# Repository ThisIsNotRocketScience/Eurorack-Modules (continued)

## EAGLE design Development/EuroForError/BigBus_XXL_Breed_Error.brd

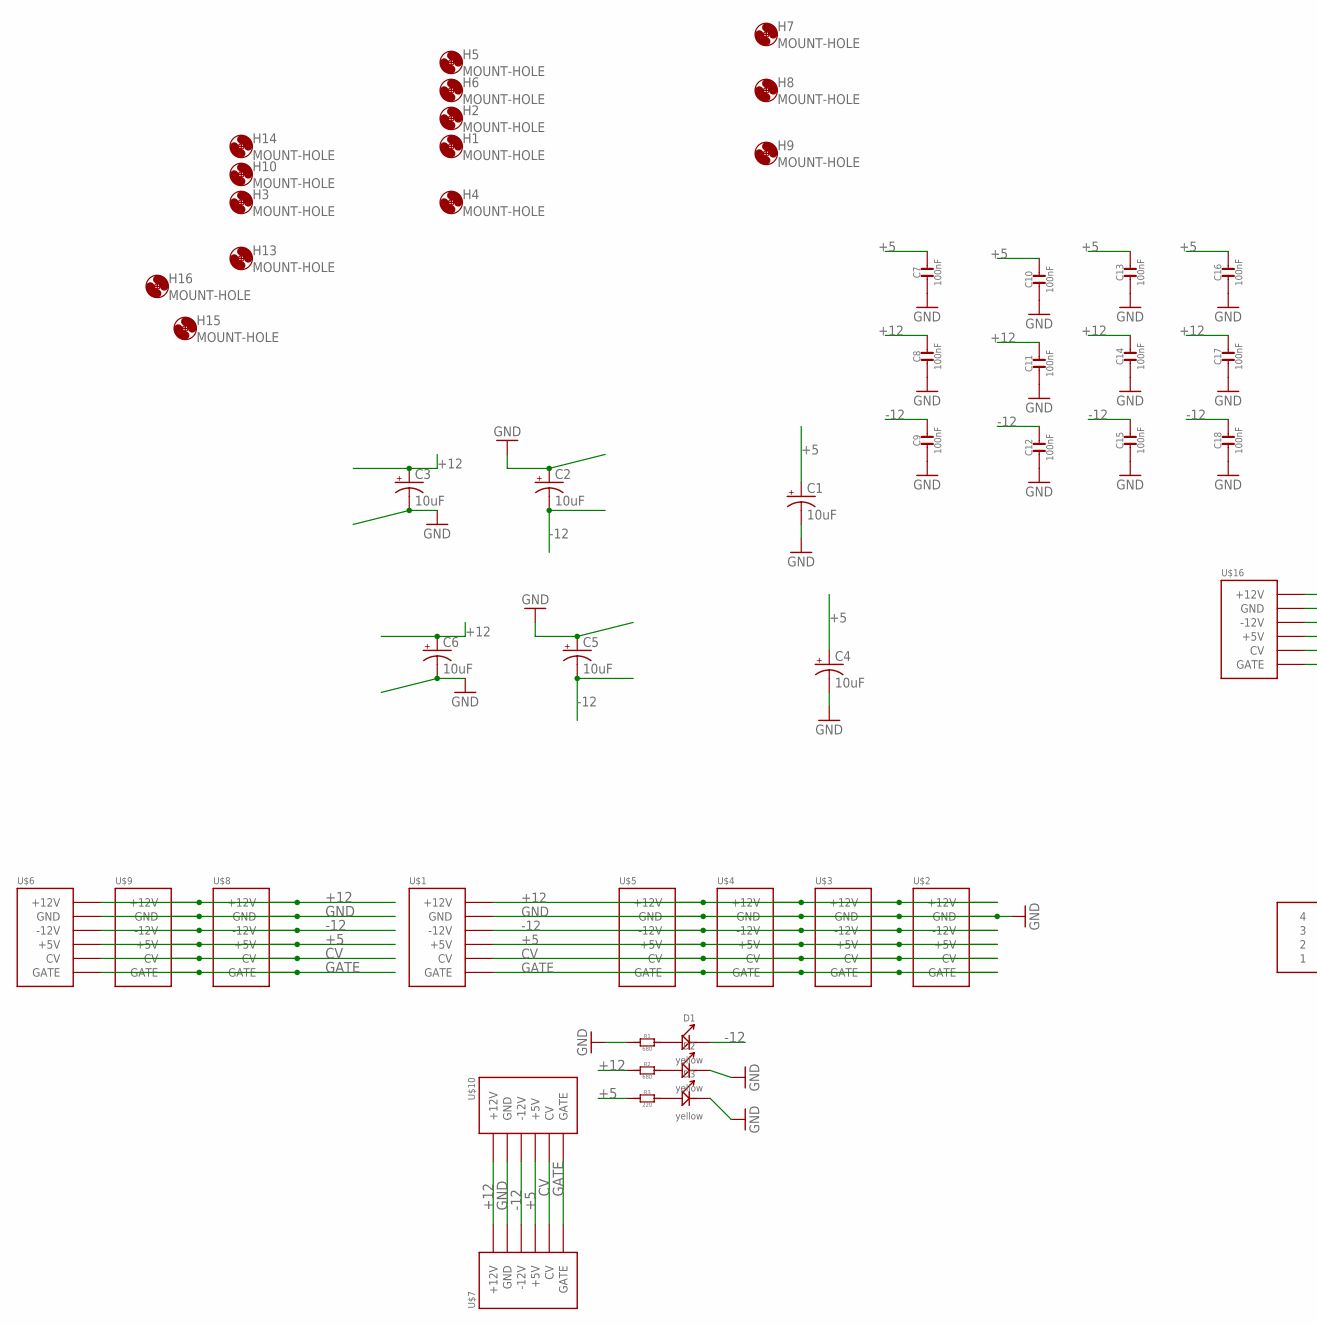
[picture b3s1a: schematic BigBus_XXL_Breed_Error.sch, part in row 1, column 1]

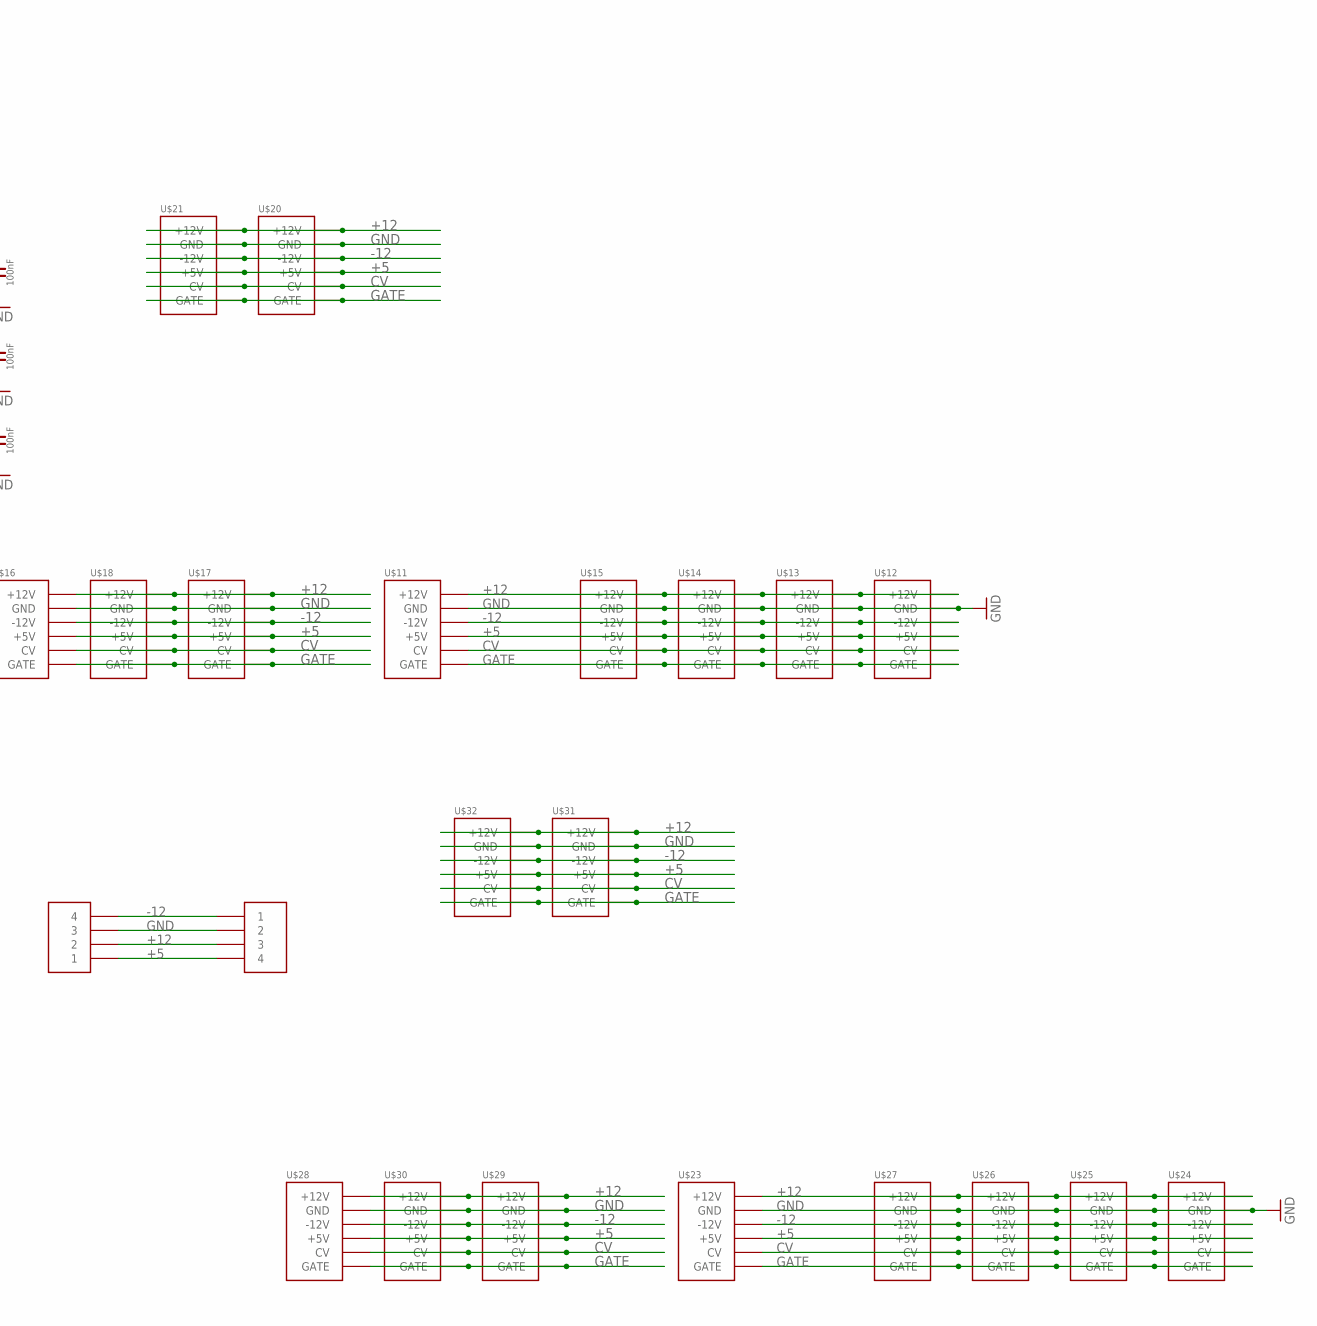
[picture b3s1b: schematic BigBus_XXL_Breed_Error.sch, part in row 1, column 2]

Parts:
C1, C2, C3, C4, C5, C6: 10uF; PANASONIC_D
C7, C8, C9, C10, C11, C12, C13, C14, C15, C16, C17, C18: 100nF; C0603
D1, D2, D3: yellow; LED0603
H1, H2, H3, H4, H5, H6, H7, H8, H9, H10, H13, H14, H15, H16: MOUNT-HOLE; 3.2-NOMARKINGS-SMALLSAFEZONE
R1, R2: 680; R0603
R3: 220; R0603
U$1, U$2, U$3, U$4, U$5, U$6, U$7, U$8, U$9, U$10, U$11, U$12, U$13, U$14, U$15, U$16, U$17, U$18, U$20, U$21, U$23, U$24, U$25, U$26, U$27, U$28, U$29, U$30, U$31, U$32: POWER_SHROUDED_NOTEXT; POWER_16_SHROUDED_NOTEXT
U$19, U$22: 4PIN5MM

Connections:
+5: C1.+, C4.+, C7.2, C10.2, C13.2, C16.2, R3.1, U$1.11 (+5V), U$1.12 (+5V), U$2.11 (+5V), U$2.12 (+5V), U$3.11 (+5V), U$3.12 (+5V), U$4.11 (+5V), U$4.12 (+5V), U$5.11 (+5V), U$5.12 (+5V), U$6.11 (+5V), U$6.12 (+5V), U$7.11 (+5V), U$7.12 (+5V), U$8.11 (+5V), U$8.12 (+5V), U$9.11 (+5V), U$9.12 (+5V), U$10.11 (+5V), U$10.12 (+5V), U$11.11 (+5V), U$11.12 (+5V), U$12.11 (+5V), U$12.12 (+5V), U$13.11 (+5V), U$13.12 (+5V), U$14.11 (+5V), U$14.12 (+5V), U$15.11 (+5V), U$15.12 (+5V), U$16.11 (+5V), U$16.12 (+5V), U$17.11 (+5V), U$17.12 (+5V), U$18.11 (+5V), U$18.12 (+5V), U$19.4, U$20.11 (+5V), U$20.12 (+5V), U$21.11 (+5V), U$21.12 (+5V), U$22.1, U$23.11 (+5V), U$23.12 (+5V), U$24.11 (+5V), U$24.12 (+5V), U$25.11 (+5V), U$25.12 (+5V), U$26.11 (+5V), U$26.12 (+5V), U$27.11 (+5V), U$27.12 (+5V), U$28.11 (+5V), U$28.12 (+5V), U$29.11 (+5V), U$29.12 (+5V), U$30.11 (+5V), U$30.12 (+5V), U$31.11 (+5V), U$31.12 (+5V), U$32.11 (+5V), U$32.12 (+5V)
+12: C3.+, C6.+, C8.2, C11.2, C14.2, C17.2, R2.1, U$1.9 (+12V), U$1.10 (+12V), U$2.9 (+12V), U$2.10 (+12V), U$3.9 (+12V), U$3.10 (+12V), U$4.9 (+12V), U$4.10 (+12V), U$5.9 (+12V), U$5.10 (+12V), U$6.9 (+12V), U$6.10 (+12V), U$7.9 (+12V), U$7.10 (+12V), U$8.9 (+12V), U$8.10 (+12V), U$9.9 (+12V), U$9.10 (+12V), U$10.9 (+12V), U$10.10 (+12V), U$11.9 (+12V), U$11.10 (+12V), U$12.9 (+12V), U$12.10 (+12V), U$13.9 (+12V), U$13.10 (+12V), U$14.9 (+12V), U$14.10 (+12V), U$15.9 (+12V), U$15.10 (+12V), U$16.9 (+12V), U$16.10 (+12V), U$17.9 (+12V), U$17.10 (+12V), U$18.9 (+12V), U$18.10 (+12V), U$19.3, U$20.9 (+12V), U$20.10 (+12V), U$21.9 (+12V), U$21.10 (+12V), U$22.2, U$23.9 (+12V), U$23.10 (+12V), U$24.9 (+12V), U$24.10 (+12V), U$25.9 (+12V), U$25.10 (+12V), U$26.9 (+12V), U$26.10 (+12V), U$27.9 (+12V), U$27.10 (+12V), U$28.9 (+12V), U$28.10 (+12V), U$29.9 (+12V), U$29.10 (+12V), U$30.9 (+12V), U$30.10 (+12V), U$31.9 (+12V), U$31.10 (+12V), U$32.9 (+12V), U$32.10 (+12V)
-12: C2.-, C5.-, C9.2, C12.2, C15.2, C18.2, D1.-, U$1.1 (-12V), U$1.2 (-12V), U$2.1 (-12V), U$2.2 (-12V), U$3.1 (-12V), U$3.2 (-12V), U$4.1 (-12V), U$4.2 (-12V), U$5.1 (-12V), U$5.2 (-12V), U$6.1 (-12V), U$6.2 (-12V), U$7.1 (-12V), U$7.2 (-12V), U$8.1 (-12V), U$8.2 (-12V), U$9.1 (-12V), U$9.2 (-12V), U$10.1 (-12V), U$10.2 (-12V), U$11.1 (-12V), U$11.2 (-12V), U$12.1 (-12V), U$12.2 (-12V), U$13.1 (-12V), U$13.2 (-12V), U$14.1 (-12V), U$14.2 (-12V), U$15.1 (-12V), U$15.2 (-12V), U$16.1 (-12V), U$16.2 (-12V), U$17.1 (-12V), U$17.2 (-12V), U$18.1 (-12V), U$18.2 (-12V), U$19.1, U$20.1 (-12V), U$20.2 (-12V), U$21.1 (-12V), U$21.2 (-12V), U$22.4, U$23.1 (-12V), U$23.2 (-12V), U$24.1 (-12V), U$24.2 (-12V), U$25.1 (-12V), U$25.2 (-12V), U$26.1 (-12V), U$26.2 (-12V), U$27.1 (-12V), U$27.2 (-12V), U$28.1 (-12V), U$28.2 (-12V), U$29.1 (-12V), U$29.2 (-12V), U$30.1 (-12V), U$30.2 (-12V), U$31.1 (-12V), U$31.2 (-12V), U$32.1 (-12V), U$32.2 (-12V)
CV: U$1.13 (CV), U$1.14 (CV), U$2.13 (CV), U$2.14 (CV), U$3.13 (CV), U$3.14 (CV), U$4.13 (CV), U$4.14 (CV), U$5.13 (CV), U$5.14 (CV), U$6.13 (CV), U$6.14 (CV), U$7.13 (CV), U$7.14 (CV), U$8.13 (CV), U$8.14 (CV), U$9.13 (CV), U$9.14 (CV), U$10.13 (CV), U$10.14 (CV), U$11.13 (CV), U$11.14 (CV), U$12.13 (CV), U$12.14 (CV), U$13.13 (CV), U$13.14 (CV), U$14.13 (CV), U$14.14 (CV), U$15.13 (CV), U$15.14 (CV), U$16.13 (CV), U$16.14 (CV), U$17.13 (CV), U$17.14 (CV), U$18.13 (CV), U$18.14 (CV), U$20.13 (CV), U$20.14 (CV), U$21.13 (CV), U$21.14 (CV), U$23.13 (CV), U$23.14 (CV), U$24.13 (CV), U$24.14 (CV), U$25.13 (CV), U$25.14 (CV), U$26.13 (CV), U$26.14 (CV), U$27.13 (CV), U$27.14 (CV), U$28.13 (CV), U$28.14 (CV), U$29.13 (CV), U$29.14 (CV), U$30.13 (CV), U$30.14 (CV), U$31.13 (CV), U$31.14 (CV), U$32.13 (CV), U$32.14 (CV)
GATE: U$1.15 (GATE), U$1.16 (GATE), U$2.15 (GATE), U$2.16 (GATE), U$3.15 (GATE), U$3.16 (GATE), U$4.15 (GATE), U$4.16 (GATE), U$5.15 (GATE), U$5.16 (GATE), U$6.15 (GATE), U$6.16 (GATE), U$7.15 (GATE), U$7.16 (GATE), U$8.15 (GATE), U$8.16 (GATE), U$9.15 (GATE), U$9.16 (GATE), U$10.15 (GATE), U$10.16 (GATE), U$11.15 (GATE), U$11.16 (GATE), U$12.15 (GATE), U$12.16 (GATE), U$13.15 (GATE), U$13.16 (GATE), U$14.15 (GATE), U$14.16 (GATE), U$15.15 (GATE), U$15.16 (GATE), U$16.15 (GATE), U$16.16 (GATE), U$17.15 (GATE), U$17.16 (GATE), U$18.15 (GATE), U$18.16 (GATE), U$20.15 (GATE), U$20.16 (GATE), U$21.15 (GATE), U$21.16 (GATE), U$23.15 (GATE), U$23.16 (GATE), U$24.15 (GATE), U$24.16 (GATE), U$25.15 (GATE), U$25.16 (GATE), U$26.15 (GATE), U$26.16 (GATE), U$27.15 (GATE), U$27.16 (GATE), U$28.15 (GATE), U$28.16 (GATE), U$29.15 (GATE), U$29.16 (GATE), U$30.15 (GATE), U$30.16 (GATE), U$31.15 (GATE), U$31.16 (GATE), U$32.15 (GATE), U$32.16 (GATE)
GND: C1.-, C2.+, C3.-, C4.-, C5.+, C6.-, C7.1, C8.1, C9.1, C10.1, C11.1, C12.1, C13.1, C14.1, C15.1, C16.1, C17.1, C18.1, D2.-, D3.-, R1.1, U$1.3 (GND), U$1.4 (GND), U$1.5 (GND), U$1.6 (GND), U$1.7 (GND), U$1.8 (GND), U$2.3 (GND), U$2.4 (GND), U$2.5 (GND), U$2.6 (GND), U$2.7 (GND), U$2.8 (GND), U$3.3 (GND), U$3.4 (GND), U$3.5 (GND), U$3.6 (GND), U$3.7 (GND), U$3.8 (GND), U$4.3 (GND), U$4.4 (GND), U$4.5 (GND), U$4.6 (GND), U$4.7 (GND), U$4.8 (GND), U$5.3 (GND), U$5.4 (GND), U$5.5 (GND), U$5.6 (GND), U$5.7 (GND), U$5.8 (GND), U$6.3 (GND), U$6.4 (GND), U$6.5 (GND), U$6.6 (GND), U$6.7 (GND), U$6.8 (GND), U$7.3 (GND), U$7.4 (GND), U$7.5 (GND), U$7.6 (GND), U$7.7 (GND), U$7.8 (GND), U$8.3 (GND), U$8.4 (GND), U$8.5 (GND), U$8.6 (GND), U$8.7 (GND), U$8.8 (GND), U$9.3 (GND), U$9.4 (GND), U$9.5 (GND), U$9.6 (GND), U$9.7 (GND), U$9.8 (GND), U$10.3 (GND), U$10.4 (GND), U$10.5 (GND), U$10.6 (GND), U$10.7 (GND), U$10.8 (GND), U$11.3 (GND), U$11.4 (GND), U$11.5 (GND), U$11.6 (GND), U$11.7 (GND), U$11.8 (GND), U$12.3 (GND), U$12.4 (GND), U$12.5 (GND), U$12.6 (GND), U$12.7 (GND), U$12.8 (GND), U$13.3 (GND), U$13.4 (GND), U$13.5 (GND), U$13.6 (GND), U$13.7 (GND), U$13.8 (GND), U$14.3 (GND), U$14.4 (GND), U$14.5 (GND), U$14.6 (GND), U$14.7 (GND), U$14.8 (GND), U$15.3 (GND), U$15.4 (GND), U$15.5 (GND), U$15.6 (GND), U$15.7 (GND), U$15.8 (GND), U$16.3 (GND), U$16.4 (GND), U$16.5 (GND), U$16.6 (GND), U$16.7 (GND), U$16.8 (GND), U$17.3 (GND), U$17.4 (GND), U$17.5 (GND), U$17.6 (GND), U$17.7 (GND), U$17.8 (GND), U$18.3 (GND), U$18.4 (GND), U$18.5 (GND), U$18.6 (GND), U$18.7 (GND), U$18.8 (GND), U$19.2, U$20.3 (GND), U$20.4 (GND), U$20.5 (GND), U$20.6 (GND), U$20.7 (GND), U$20.8 (GND), U$21.3 (GND), U$21.4 (GND), U$21.5 (GND), U$21.6 (GND), U$21.7 (GND), U$21.8 (GND), U$22.3, U$23.3 (GND), U$23.4 (GND), U$23.5 (GND), U$23.6 (GND), U$23.7 (GND), U$23.8 (GND), U$24.3 (GND), U$24.4 (GND), U$24.5 (GND), U$24.6 (GND), U$24.7 (GND), U$24.8 (GND), U$25.3 (GND), U$25.4 (GND), U$25.5 (GND), U$25.6 (GND), U$25.7 (GND), U$25.8 (GND), U$26.3 (GND), U$26.4 (GND), U$26.5 (GND), U$26.6 (GND), U$26.7 (GND), U$26.8 (GND), U$27.3 (GND), U$27.4 (GND), U$27.5 (GND), U$27.6 (GND), U$27.7 (GND), U$27.8 (GND), U$28.3 (GND), U$28.4 (GND), U$28.5 (GND), U$28.6 (GND), U$28.7 (GND), U$28.8 (GND), U$29.3 (GND), U$29.4 (GND), U$29.5 (GND), U$29.6 (GND), U$29.7 (GND), U$29.8 (GND), U$30.3 (GND), U$30.4 (GND), U$30.5 (GND), U$30.6 (GND), U$30.7 (GND), U$30.8 (GND), U$31.3 (GND), U$31.4 (GND), U$31.5 (GND), U$31.6 (GND), U$31.7 (GND), U$31.8 (GND), U$32.3 (GND), U$32.4 (GND), U$32.5 (GND), U$32.6 (GND), U$32.7 (GND), U$32.8 (GND)
unnamed: D1.+, R1.2
unnamed: D2.+, R2.2
unnamed: D3.+, R3.2

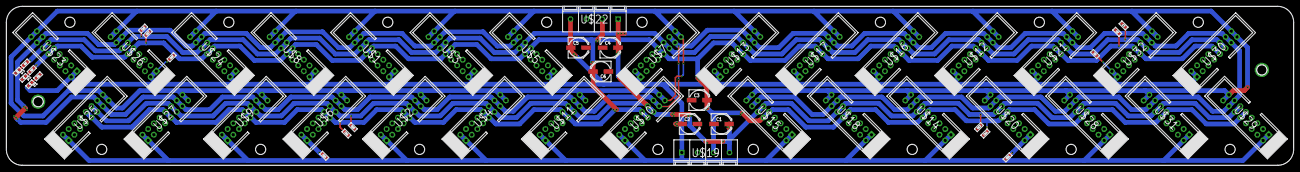
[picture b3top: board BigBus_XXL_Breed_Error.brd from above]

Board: 2 copper layers, 405.0 x 50.0 mm, 72 parts (0 on the bottom side), 9 nets.

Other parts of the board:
H11, H12: MOUNT-HOLE; 3.2-NOMARKINGS-SMALLSAFEZONE

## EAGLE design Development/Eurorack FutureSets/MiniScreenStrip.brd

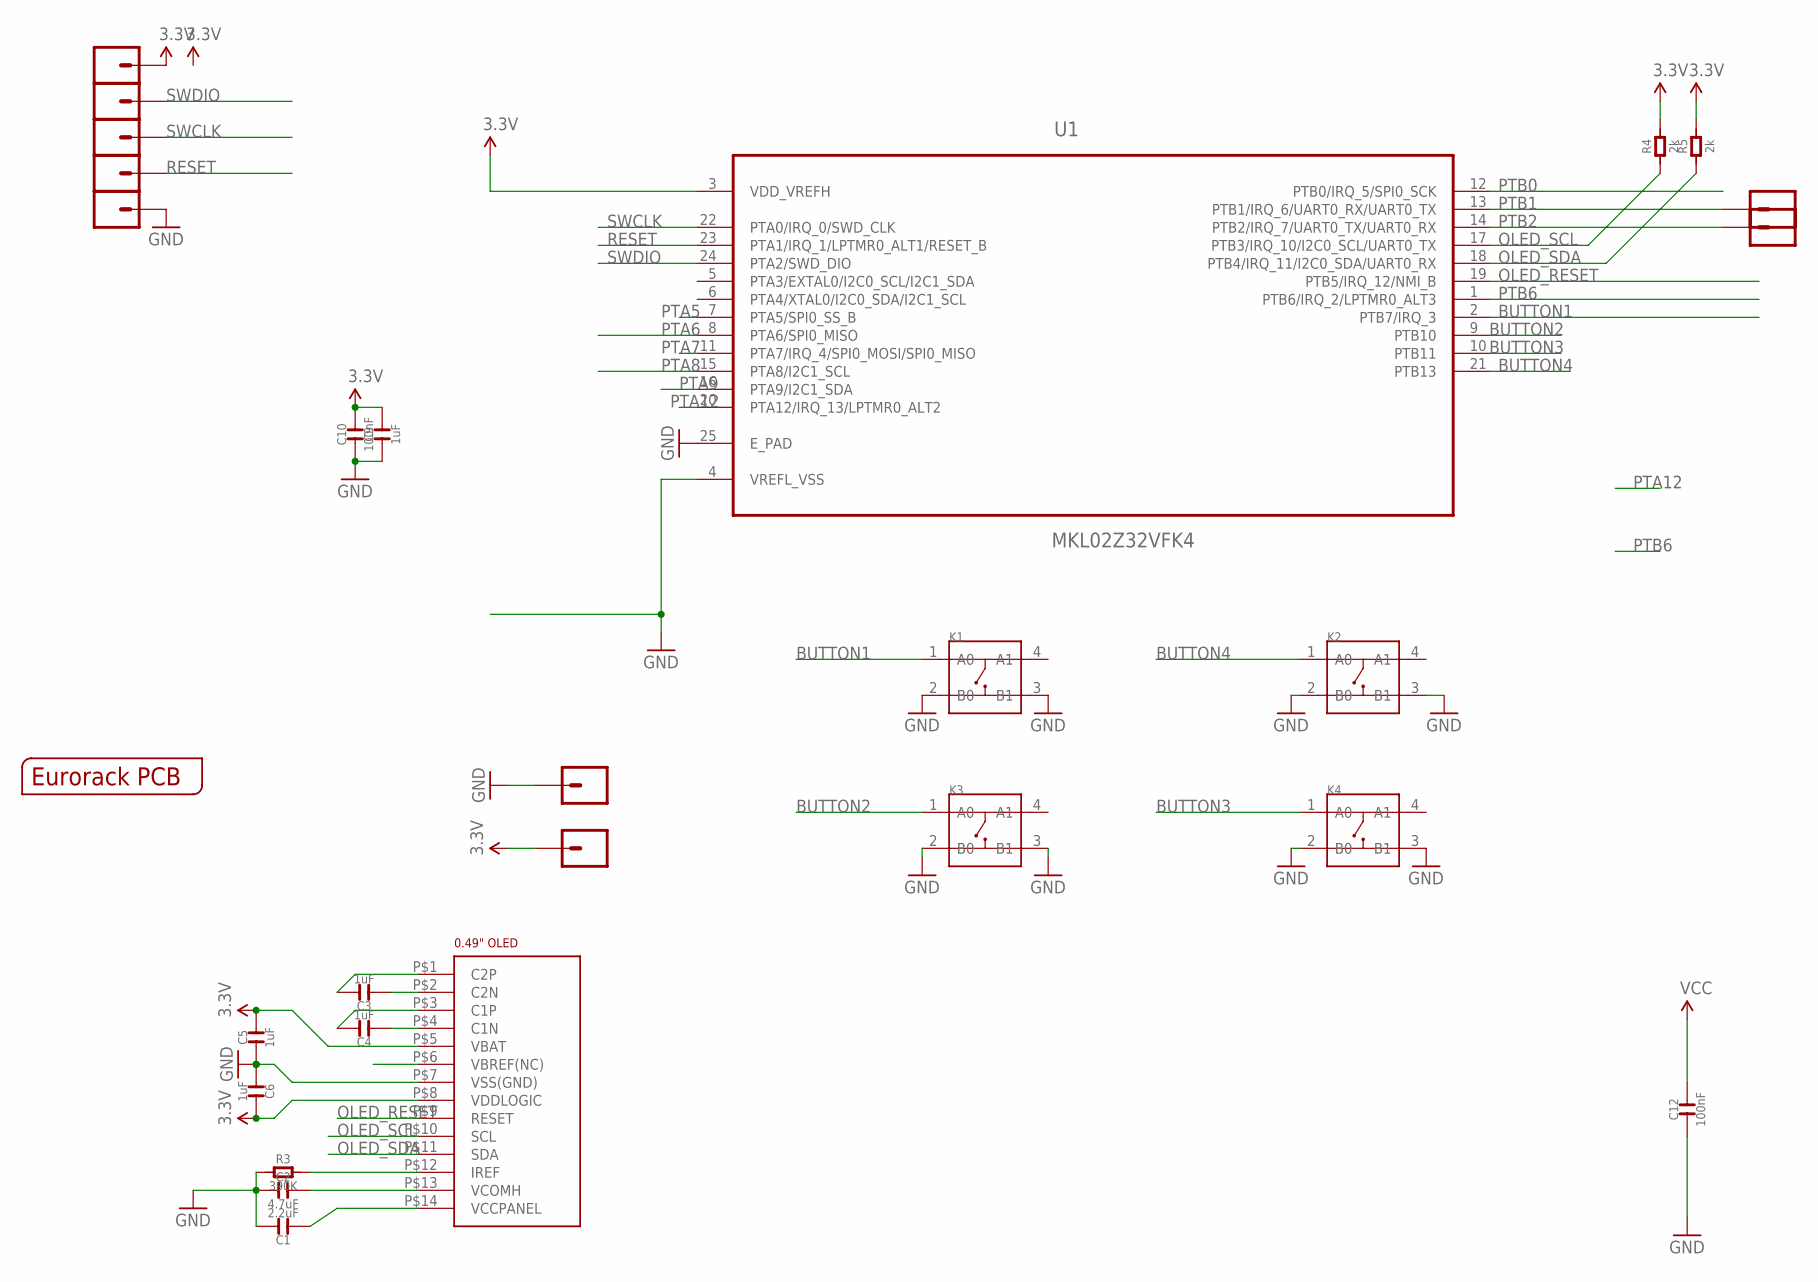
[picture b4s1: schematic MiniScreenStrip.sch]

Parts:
C1: 2.2uF; C0603
C2: 4.7uF; C0603
C3, C4, C5, C6, C9: 1uF; C0603
C10, C12: 100nF; C0603
K1, K2, K3, K4: BUTTON-4P-3100010P1; 4P-SMD-6.0X6.0X5.0H
PTA6_MISO1, PTA6_MISO2, PTA6_MISO3, PTA6_MISO4, PTA6_MISO5: M01SMD-4.5X1.5; PAD-1.5X4.5
PTB1_RXTX, PTB2_TXRX, PTB2_TXRX1, PTB2_TXRX2: M01SMD-4.5X1.5; PAD-1.5X4.5
R3: 390K; R0603
R4, R5: 2k; R0603
U1: MKL02Z32VFK4; QFN50P400X400X100-25N
U$1: 0.49"OLEDFOLDED; 0.49"-FPC-0.7-14-FOLDED
U$2: EURORACK_PCB4HP; EURORACK4HPPCB

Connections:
3.3V: C5.2, C6.2, C9.2, C10.2, C12.2, PTA6_MISO1.P$1, PTB2_TXRX1.P$1, R4.2, R5.2, U1.3 (VDD_VREFH), U$1.P$5 (VBAT), U$1.P$8 (VDDLOGIC)
BUTTON1: K1.1 (A0), U1.2 (PTB7/IRQ_3)
BUTTON2: K3.1 (A0), U1.9 (PTB10)
BUTTON3: K4.1 (A0), U1.10 (PTB11)
BUTTON4: K2.1 (A0), U1.21 (PTB13)
GND: C1.2, C2.1, C5.1, C6.1, C9.1, C10.1, C12.1, K1.2 (B0), K1.3 (B1), K2.2 (B0), K2.3 (B1), K3.2 (B0), K3.3 (B1), K4.2 (B0), K4.3 (B1), PTA6_MISO5.P$1, PTB2_TXRX2.P$1, R3.1, U1.4 (VREFL_VSS), U1.25 (E_PAD), U$1.P$7 (VSS(GND))
unnamed: C3.2, U$1.P$1 (C2P)
unnamed: C4.2, U$1.P$3 (C1P)
unnamed: R3.2, U$1.P$12 (IREF)
unnamed: C1.1, U$1.P$14 (VCCPANEL)
unnamed: C2.2, U$1.P$13 (VCOMH)
unnamed: C3.1, U$1.P$2 (C2N)
unnamed: C4.1, U$1.P$4 (C1N)
OLED_RESET: U1.19 (PTB5/IRQ_12/NMI_B), U$1.P$9 (RESET)
OLED_SCL: R4.1, U1.17 (PTB3/IRQ_10/I2C0_SCL/UART0_TX), U$1.P$10 (SCL)
OLED_SDA: R5.1, U1.18 (PTB4/IRQ_11/I2C0_SDA/UART0_RX), U$1.P$11 (SDA)
PTA5: U1.7 (PTA5/SPI0_SS_B)
PTA6: U1.8 (PTA6/SPI0_MISO)
PTA7: U1.11 (PTA7/IRQ_4/SPI0_MOSI/SPI0_MISO)
PTA8: U1.15 (PTA8/I2C1_SCL)
PTA9: U1.16 (PTA9/I2C1_SDA)
PTA12: U1.20 (PTA12/IRQ_13/LPTMR0_ALT2)
PTB0: U1.12 (PTB0/IRQ_5/SPI0_SCK)
PTB1: PTB1_RXTX.P$1, U1.13 (PTB1/IRQ_6/UART0_RX/UART0_TX)
PTB2: PTB2_TXRX.P$1, U1.14 (PTB2/IRQ_7/UART0_TX/UART0_RX)
PTB6: U1.1 (PTB6/IRQ_2/LPTMR0_ALT3)
RESET: PTA6_MISO4.P$1, U1.23 (PTA1/IRQ_1/LPTMR0_ALT1/RESET_B)
SWCLK: PTA6_MISO3.P$1, U1.22 (PTA0/IRQ_0/SWD_CLK)
SWDIO: PTA6_MISO2.P$1, U1.24 (PTA2/SWD_DIO)

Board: 2 copper layers, 28 parts (5 on the bottom side), 21 nets, no tracks yet.
